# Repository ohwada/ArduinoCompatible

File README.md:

# ArduinoCompatible

Arduino Compatible Board

## Directories
- arduino_1
Arduino Uno Without USB Serial

## Blog (in Japanese)
http://android.ohwada.jp/archives/5593

## Photo

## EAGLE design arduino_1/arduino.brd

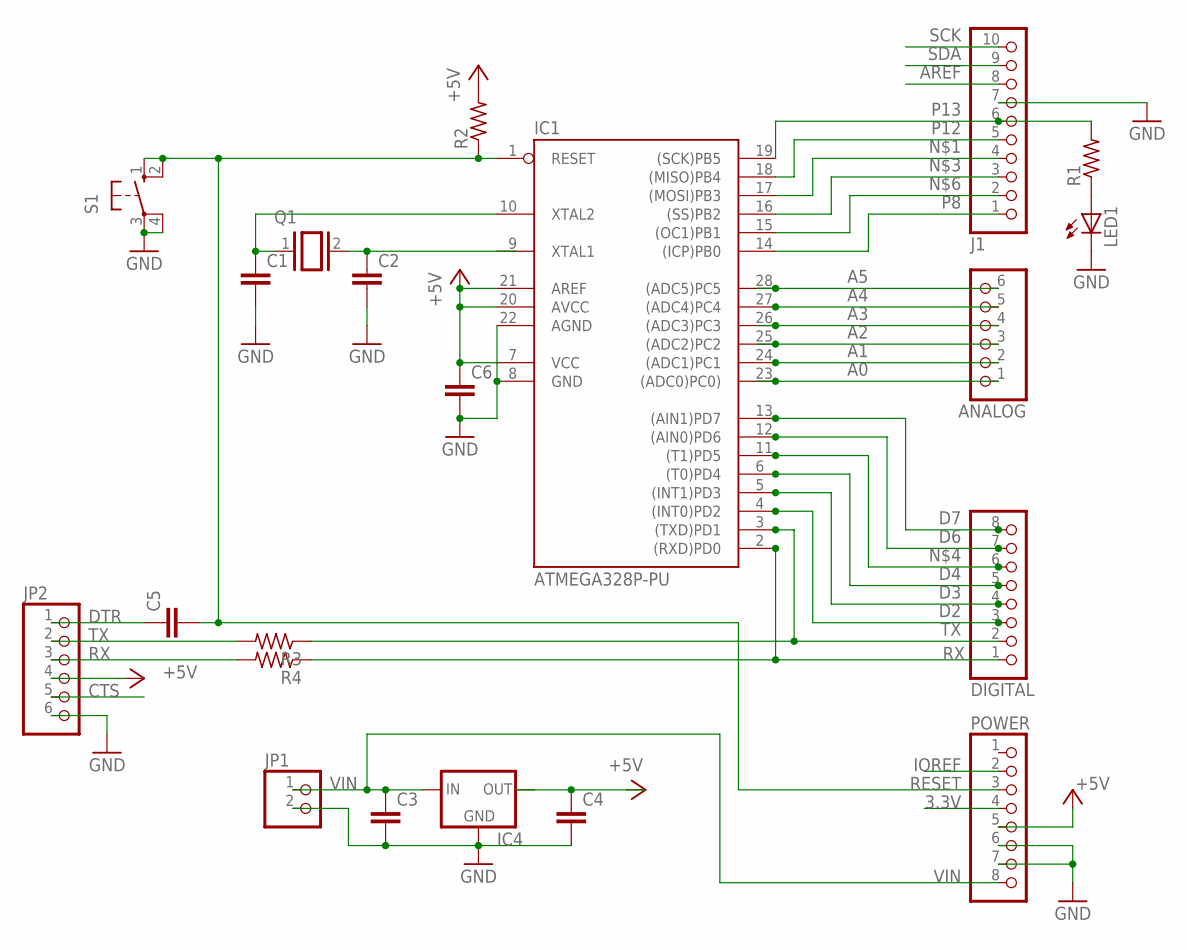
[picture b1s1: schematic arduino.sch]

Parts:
ANALOG: PINHD-1X6; 1X06
C1, C2, C3, C4, C5, C6: C-EU050-025X075; C050-025X075
DIGITAL: PINHD-1X8TH; 1X08-TH
IC1: ATMEGA328P-PU; DIL28-3
IC4: 78XXS
J1: PINHD-1X10TH; 1X10-TH
JP1: PINHD-1X2; 1X02
JP2: PINHD-1X6; 1X06
LED1: LED3MM
POWER: PINHD-1X8TH; 1X08-TH
Q1: XTAL/S; QS
R1, R2, R3, R4: R-US_0207/10; 0207/10
S1: 10-XX; B3F-10XX

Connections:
3.3V: POWER.4
A0: ANALOG.1, IC1.23 ((ADC0)PC0))
A1: ANALOG.2, IC1.24 ((ADC1)PC1)
A2: ANALOG.3, IC1.25 ((ADC2)PC2)
A3: ANALOG.4, IC1.26 ((ADC3)PC3)
A4: ANALOG.5, IC1.27 ((ADC4)PC4)
A5: ANALOG.6, IC1.28 ((ADC5)PC5)
AREF: J1.8
CTS: JP2.5
D2: DIGITAL.3, IC1.4 ((INT0)PD2)
D3: DIGITAL.4, IC1.5 ((INT1)PD3)
D4: DIGITAL.5, IC1.6 ((T0)PD4)
D6: DIGITAL.7, IC1.12 ((AIN0)PD6)
D7: DIGITAL.8, IC1.13 ((AIN1)PD7)
DTR: C5.1, JP2.1
IOREF: POWER.2
unnamed: IC1.17 ((MOSI)PB3), J1.4
unnamed: JP2.2, R3.2
unnamed: IC1.16 ((SS)PB2), J1.3
unnamed: DIGITAL.6, IC1.11 ((T1)PD5)
unnamed: C4.1, C6.1, IC1.7 (VCC), IC1.20 (AVCC), IC1.21 (AREF), IC4.OUT, JP2.4, POWER.5, R2.2
unnamed: IC1.15 ((OC1)PB1), J1.2
unnamed: JP2.3, R4.2
unnamed: C2.1, IC1.9 (XTAL1), Q1.2
unnamed: C1.1, IC1.10 (XTAL2), Q1.1
unnamed: LED1.A, R1.1
unnamed: C1.2, C2.2, C3.2, C4.2, C6.2, IC1.8 (GND), IC1.22 (AGND), IC4.GND, J1.7, JP1.2, JP2.6, LED1.K (C), POWER.6, POWER.7, S1.3, S1.4 (P1)
P8: IC1.14 ((ICP)PB0), J1.1
P12: IC1.18 ((MISO)PB4), J1.5
P13: IC1.19 ((SCK)PB5), J1.6, R1.2
RESET: C5.2, IC1.1 (RESET), POWER.3, R2.1, S1.1 (S), S1.2 (S1)
RX: DIGITAL.1, IC1.2 ((RXD)PD0), R4.1
SCK: J1.10
SDA: J1.9
TX: DIGITAL.2, IC1.3 ((TXD)PD1), R3.1
VIN: C3.1, IC4.IN, JP1.1, POWER.8

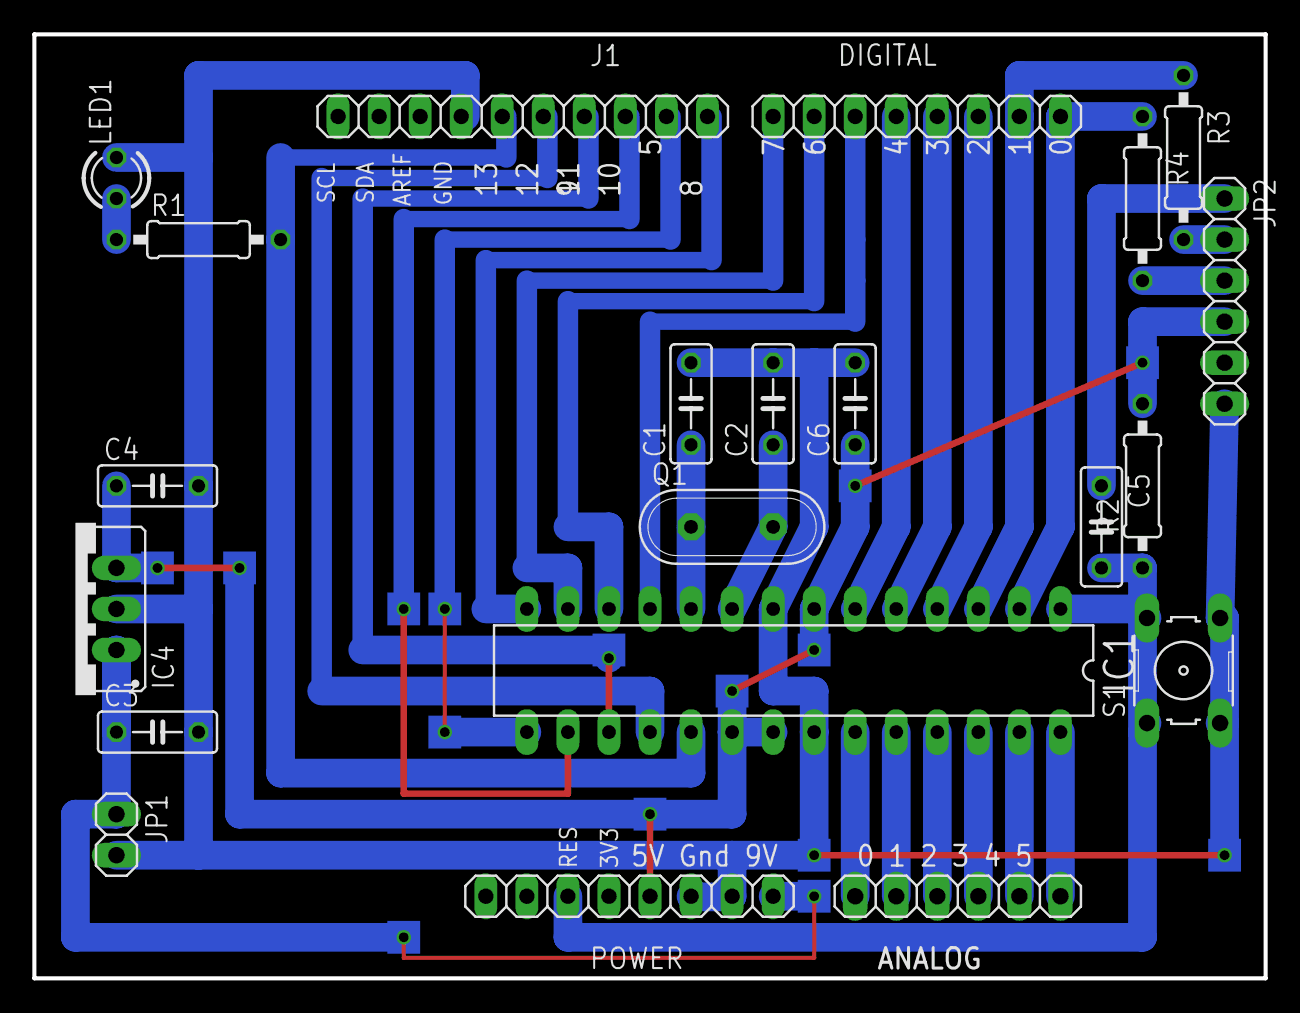
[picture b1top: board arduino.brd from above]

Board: 2 copper layers, 76.2 x 58.4 mm, 21 parts (0 on the bottom side), 30 nets.

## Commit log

2015-02-27 FirstVersion
2015-02-27 FristVersion
2015-02-27 FirstVrsiom
